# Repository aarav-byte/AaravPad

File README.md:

# AaravPad

A 3x3 macropad I made for Hackpad. 9 keys, a XIAO RP2040, running KMK.

## Why

I wanted to make something start to finish myself: PCB, case, firmware, all of it. A macropad seemed like a good first project, and it's something I'll actually use.

## What went wrong

- I built the first version around a Pro Micro before realising it isn't on the approved parts list, so I had to swap it for the XIAO and redo the wiring.
- The USB port was sitting way inside the board, so you couldn't plug a cable in once it was in the case. I had to move it to the edge and resize the board.
- Getting the 3D models to show up in KiCad took way longer than it should have.

## Schematic

## PCB

2 layer board, around 89 x 63 mm.

## Case

Two printed parts, a top plate and a bottom tray. The switches clip into the plate, the PCB gets soldered to them, and 4 M3 screws go through the top into heat-set inserts in the bottom.

## BOM

- 1x Seeed XIAO RP2040
- 9x MX switches
- 9x 1N4148 diodes
- 9x DSA keycaps
- 4x M3x16 screws
- 4x M3 heat-set inserts
- 1x PCB
- 3D printed case (top + bottom)

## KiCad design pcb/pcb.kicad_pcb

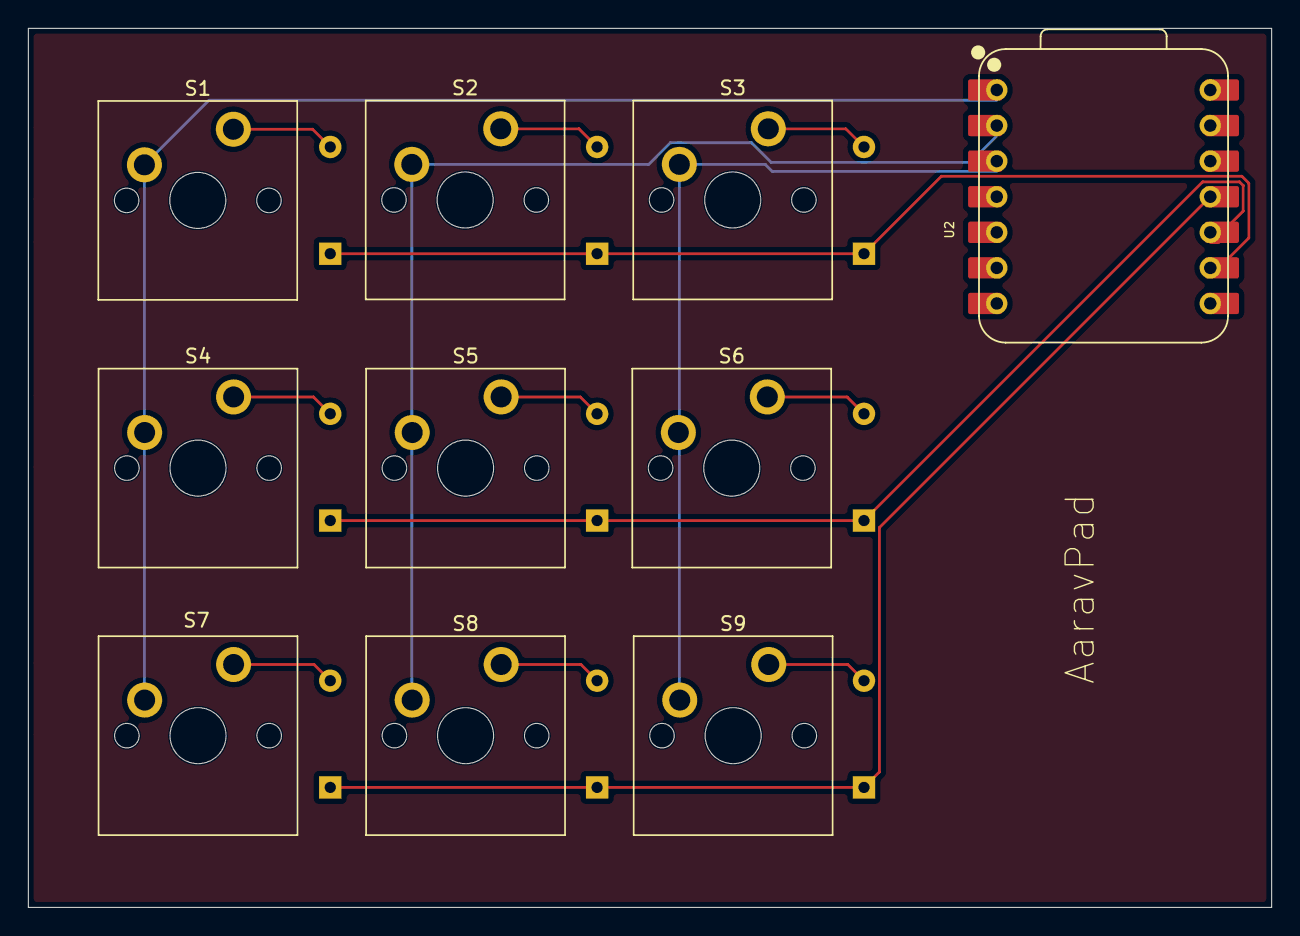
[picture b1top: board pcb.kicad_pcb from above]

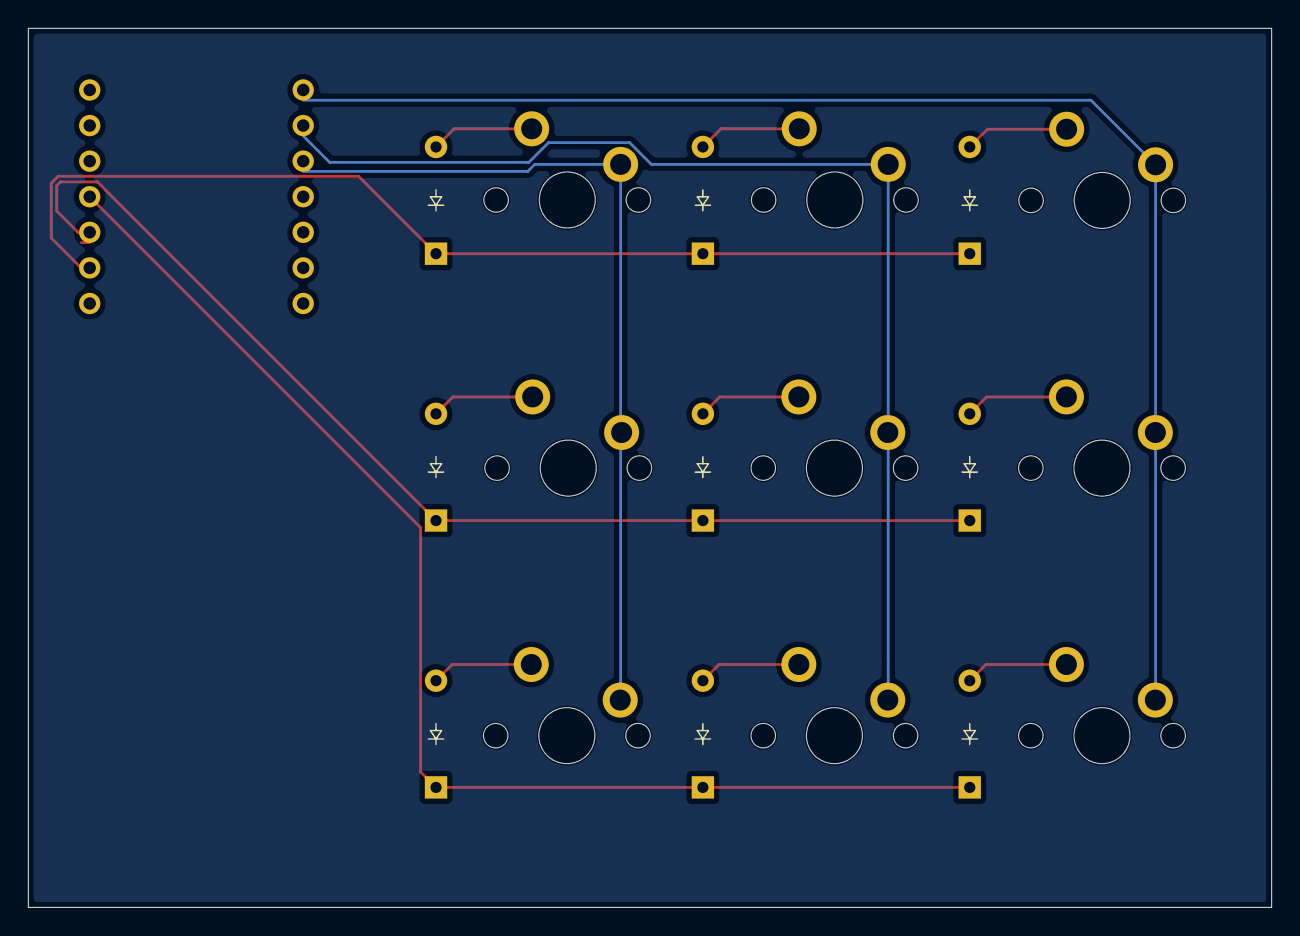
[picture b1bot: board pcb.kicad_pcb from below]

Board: 2 copper layers, 88.8 x 62.8 mm, 19 parts (9 on the bottom side), 15 nets.

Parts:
D1, D2, D3, D4, D5, D6, D7, D8, D9: Diode_DO-35
S1, S2, S3, S4, S5, S6, S7, S8, S9: MX_PCB_1.00u
U2: XIAO-RP2040-SMD; XIAO-RP2040-DIP

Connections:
unnamed: D1.2 (A), S1.2
unnamed: D2.2 (A), S2.2
unnamed: D3.2 (A), S3.2
unnamed: D4.2 (A), S4.2
unnamed: D5.2 (A), S5.2
unnamed: D6.2 (A), S6.2
unnamed: D7.2 (A), S7.2
unnamed: D8.2 (A), S8.2
unnamed: D9.2 (A), S9.2
col_0: S1.1, S4.1, S7.1, U2.1 (D0)
col_1: S2.1, S5.1, S8.1, U2.2 (D1)
col_2: S3.1, S6.1, S9.1, U2.3 (D2)
row_0: D1.1 (K), D2.1 (K), D3.1 (K), U2.9 (D8)
row_1: D4.1 (K), D5.1 (K), D6.1 (K), U2.10 (D9)
row_2: D7.1 (K), D8.1 (K), D9.1 (K), U2.11 (D10)
